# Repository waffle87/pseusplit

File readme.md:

# Pseusplit

A pseudo-split keyboard with a trackpad or LCD display and per-key RGB

## Hardware Specifics
This keyboard uses an integrated STM32G0B1 microcontroller fit with a single push button switch<sup>[1](#references)</sup>, and USB-C. It also features a dedicated IS31FL3733 RGB Matrix driver to alleviate processing power from the primary MCU for LCD drawing, or other tasks.

## Ordering
The following instructions will be for [JLCPCB](jlcpcb.com), but should generally apply to most PCB manufacturers. The Gerber files in this repository include:
- [**pcb_gerbers.zip**](production/pcb_gerbers.zip): Main PCB
- [**plate_gerbers.zip**](production/plate_gerbers.zip): Switch Plate PCB<sup>*</sup>
- [**back_gerbers.zip**](production/back_gerbers.zip): Backplate PCB

* The switch plate PCB is designed for a single half of the keyboard (and is reversible), meaning ordering a quantity of 10 will be enough to cover 5 keyboards.

1. Upload the appropriate Gerber files described above
2. Set PCB quantity and colour as desired
3. For PCB assembly, choose **Economic** PCBA type and **Bottom Side** for assembly side
4. Upload the [BOM](production/bom.csv) and [CPL](production/positions.csv) files
5. Ensure the correct components have been selected, and all are in stock. An effort has been made to choose as few extended components as possible, but this is not possible for some.
6. Give a quick look at the component placement and make sure nothing looks wildly wrong. It is normal for some components to be shown oriented incorrectly or not quite where they belong. The PCB reviewers will usually correct this without issue.

### Additional Components
For optional components to be installed by hand:
| Item | Quantity | Remarks |
|------|----------|---------|
| 6028 RGB LEDs ([Alibaba](https://www.alibaba.com/product-detail/smd-6028-RGB-led-diode-for_60637386884.html)) | 36 | Unforunately, LEDs matching this pinout are rather difficult to find, and are not carried by LCSC. |
| 4mm M2 Screws | 8 | Used for mounting PCB to plate case. Length does not have to be exact. |
| 6mm M2 Standoffs | 4 | Used for mounting PCB to plate case. Ensure maximum diameter is no greater than 4mm. |
| 240x240 LCD ([ST7789](https://www.adafruit.com/product/3787)) | 1<sup>*</sup> | Other displays with same pinout and dimensions (no larger than 40x43mm) will work. |
| Azoteq Trackpad ([TPS43](https://www.mouser.com/ProductDetail/Azoteq/TPS43-201A-B?qs=HXFqYaX1Q2x%252BNkQCZlM0ug%3D%3D)) | 1<sup>*</<sup> | Installed via soldering wires to appropriate display header pins. |
| MX Switches | 36 | Pick your favourite switches! |

* Trackpad and LCD is either/or. Both cannot be installed at the same time.

## Assembly Instructions
These steps assume you already have an assembled PCB and are installing switches, trackpad, etc. If you are hand-assembling the PCBs with all components, the [interactive BOM](https://html-preview.github.io/?url=https://github.com/waffle87/pseusplit/blob/master/ibom.html) will be handy.

1. **Compile and flash firmware.** This assumes a local QMK build environment has already been setup. Firmware sources can be found [here](https://git.pngu.org/qmk_me/keyboards/pseusplit). Enter bootloader by holding the reset button while plugging PCB in. Flash firmware using `qmk flash` or QMK Toolbox.
2. **Ensure the keyboard is functional** by shorting switch footprint pins with metal tweezers. This should output keypresses on the computer.
3. **Install LCD display if desired.** Solder the 12 pin header to the labeled footprint on the PCB and solder display to the header. In the firmware, enable the Quantum Painter feature and disable the Pointing Device feature if necessary.
4. **Install Azoteq trackpad if desired.** Solder wires from the pins on the trackpad to the appropriate pins on the 12 pin header. Refer to schematic for specifics. In the firmware, enable the Pointing Device feature and disable the Quantum Painter feature if necessary.
5. **Install switches** by inserting a few switches into the switch plate (corners/middle), and then solder to PCB. Fill in rest of switches, testing as you go.
6. **Assemble plate case**. Insert the M2 screws into the back plate and affix standoffs to screws. Place PCB + Plate onto standoffs and install remaining 4 screws.

## References
1. [A single-push reset circuit for STM32](https://acheronproject.com/reset_article_1/reset_article_1)
2. Relevant datasheets

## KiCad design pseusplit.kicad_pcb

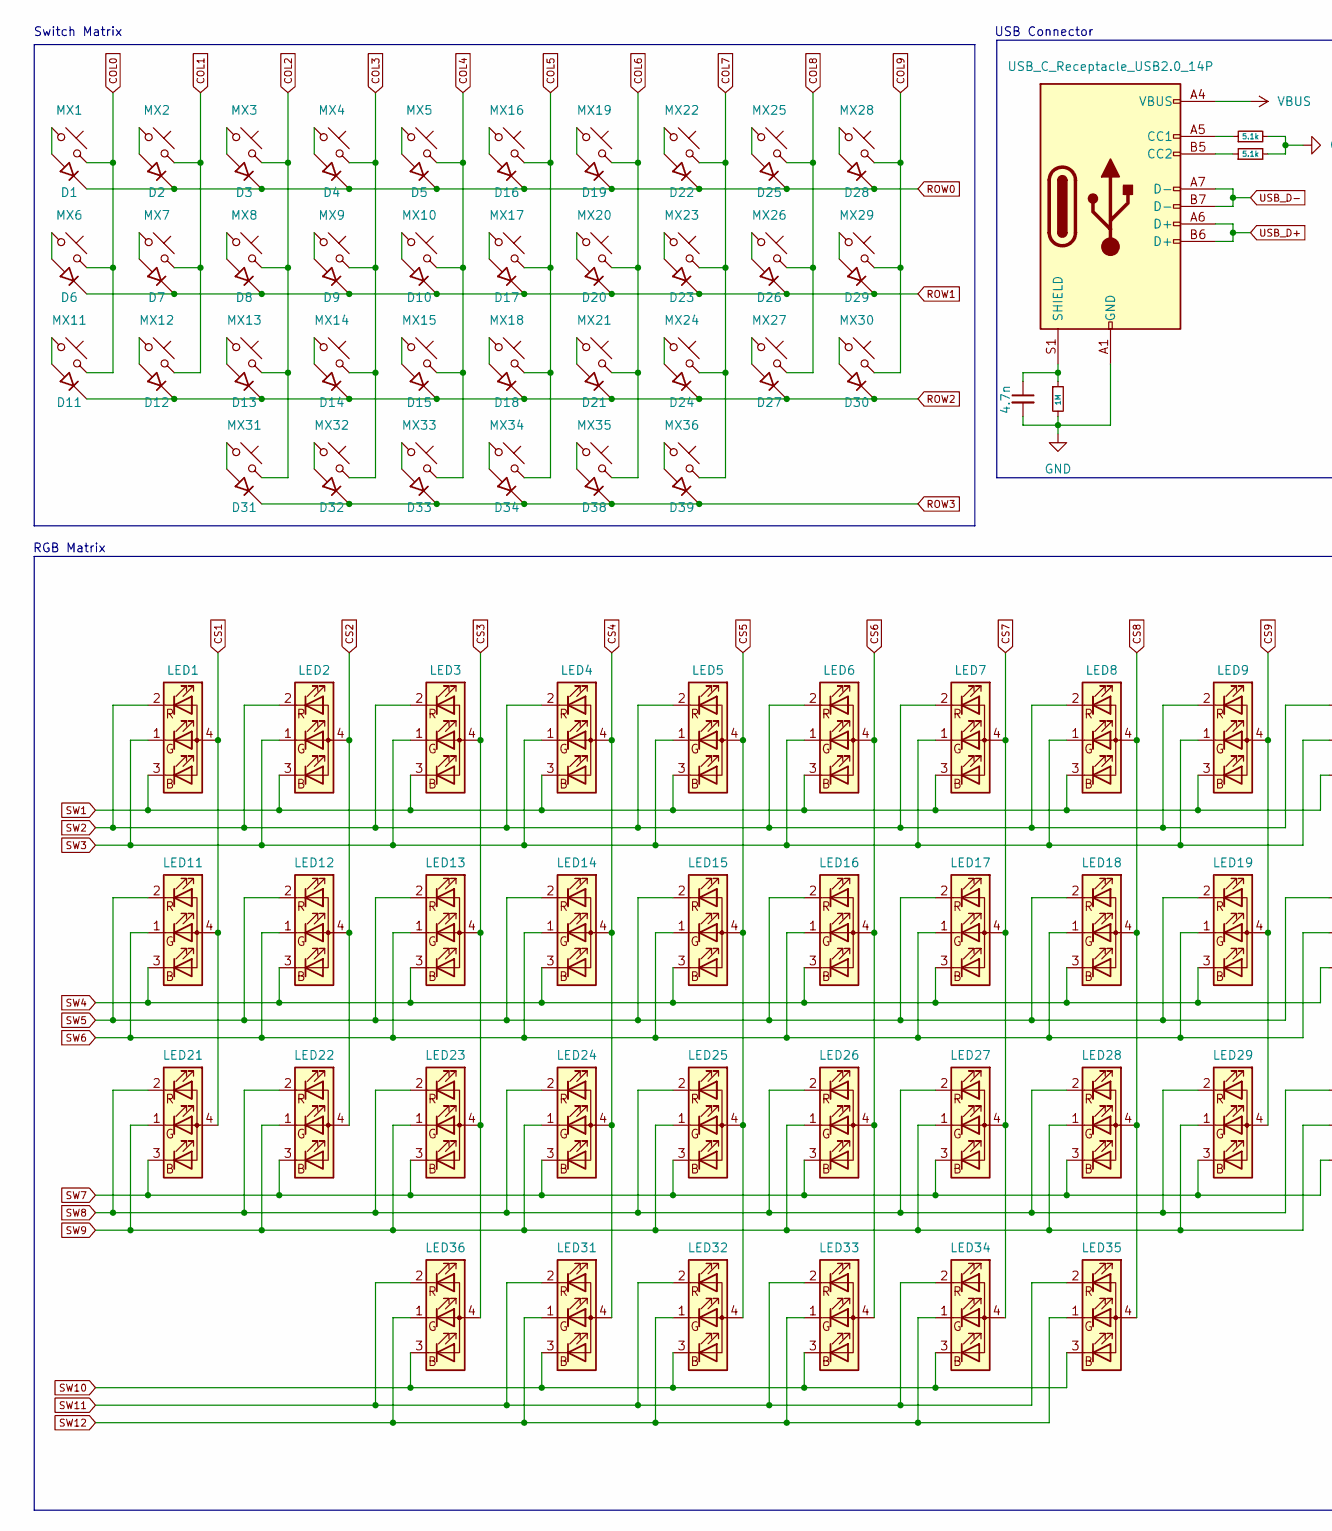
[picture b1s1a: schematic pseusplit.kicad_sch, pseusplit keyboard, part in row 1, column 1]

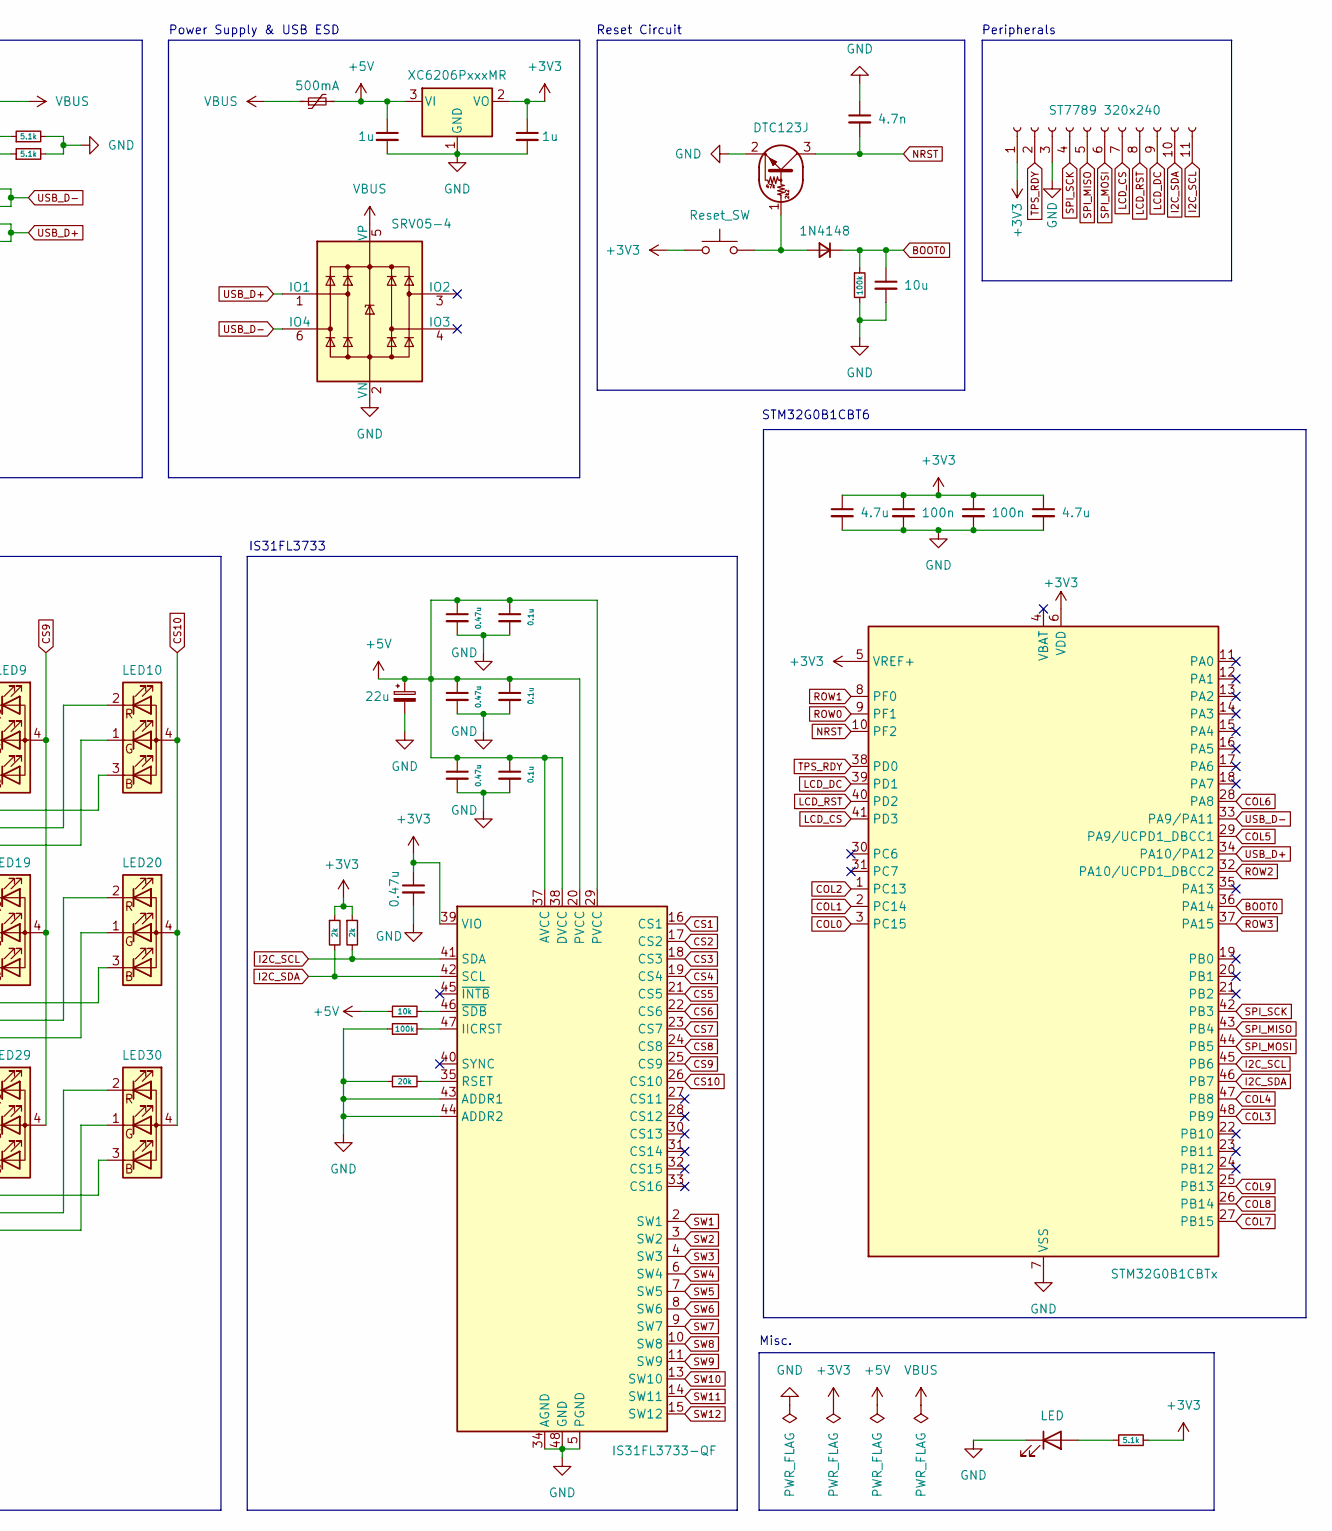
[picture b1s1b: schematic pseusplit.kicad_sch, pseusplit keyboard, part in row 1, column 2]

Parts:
C1, C2, C4, C6: 0.47u; C_0805_2012Metric; MPN C13967
C3, C5, C7: 0.1u; C_0805_2012Metric; MPN C49678
C8: 22u; C_0805_2012Metric; MPN C45783
C9, C12: 4.7n; C_0805_2012Metric; MPN C1744
C10, C11: 1u; C_0805_2012Metric; MPN C28323
C13: 10u; C_0805_2012Metric; MPN C15850
C14, C16: 100n; C_0805_2012Metric; MPN C28233
C17, C18: 4.7u; C_0805_2012Metric; MPN C1779
D1, D2, D3, D4, D5, D6, D7, D8, D9, D10, D11, D12, D13, D14, D15, D16, D17, D18, D19, D20, D21, D22, D23, D24, D25, D26, D27, D28, D29, D30, D31, D32, D33, D34, D38, D39: D_45deg; D_SOD-123; MPN C81598
D37: 1N4148; D_SOD-123; MPN C81598
D40: LED; LED_0805_2012Metric; MPN C2297
F1: 500mA; Fuse_1206_3216Metric; MPN C2830238
J1: USB_C_Receptacle_USB2.0_14P; USB_C_Receptacle_HRO_TYPE-C-31-M-12; MPN C165948
J3: ST7789 320x240; PinHeader_1x11_P2.54mm_Vertical
LED1, LED2, LED3, LED4, LED5, LED6, LED7, LED8, LED9, LED10, LED11, LED12, LED13, LED14, LED15, LED16, LED17, LED18, LED19, LED20, LED21, LED22, LED23, LED24, LED25, LED26, LED27, LED28, LED29, LED30, LED31, LED32, LED33, LED34, LED35, LED36: MX_LED_6028R; LED_MX_6028R; MPN C183826
MX1: Q; SW_MX_1u
MX2: W; SW_MX_1u
MX3: E; SW_MX_1u
MX4: R; SW_MX_1u
MX5: T; SW_MX_1u
MX6: A; SW_MX_1u
MX7: S; SW_MX_1u
MX8: D; SW_MX_1u
MX9: F; SW_MX_1u
MX10: G; SW_MX_1u
MX11: Z; SW_MX_1u
MX12: X; SW_MX_1u
MX13: C; SW_MX_1u
MX14: V; SW_MX_1u
MX15: B; SW_MX_1u
MX16: Y; SW_MX_1u
MX17: H; SW_MX_1u
MX18: N; SW_MX_1u
MX19: U; SW_MX_1u
MX20: J; SW_MX_1u
MX21: M; SW_MX_1u
MX22: I; SW_MX_1u
MX23: K; SW_MX_1u
MX24: ,; SW_MX_1u
MX25: O; SW_MX_1u
MX26: L; SW_MX_1u
MX27: .; SW_MX_1u
MX28: P; SW_MX_1u
MX29: ;; SW_MX_1u
MX30: /; SW_MX_1u
MX31: T1; SW_MX_1u
MX32: T2; SW_MX_1u
MX33: T3; SW_MX_1u
MX34: T4; SW_MX_1u
MX35: T5; SW_MX_1u
MX36: T6; SW_MX_1u
Q1: DTC123J; SOT-23; MPN C20616358
R1: 20k; R_0805_2012Metric; MPN C4328
R2, R11: 100k; R_0805_2012Metric; MPN C149504
R3: 10k; R_0805_2012Metric; MPN C17414
R4, R5: 2k; R_0805_2012Metric; MPN C17604
R6: 1M; R_0805_2012Metric; MPN C17514
R7, R8, R12: 5.1k; R_0805_2012Metric; MPN C27834
SW1: Reset_SW; SW_SPST_SKQG_WithStem; MPN C318884
U1: IS31FL3733-QF; QFN-48-1EP_6x6mm_P0.4mm_EP4.2x4.2mm; MPN C506251
U2: XC6206PxxxMR; SOT-23-3; MPN C5446
U4: STM32G0B1CBTx; LQFP-48_7x7mm_P0.5mm; MPN C2847904
U5: SRV05-4; SOT-23-6-routable; MPN C558418

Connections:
+3V3: C1.1, C11.1, C14.1, C16.1, C17.1, C18.1, J3.1, R4.1, R5.1, R12.2, SW1.1, U1.39 (VIO), U2.2 (VO), U4.5 (VREF+), U4.6 (VDD)
+5V: C2.1, C3.1, C4.1, C5.1, C6.1, C7.1, C8.1, C10.1, F1.2, R3.1, U1.20 (PVCC), U1.29 (PVCC), U1.37 (AVCC), U1.38 (DVCC), U2.3 (VI)
BOOT0: C13.1, D37.1 (K), R11.1, U4.36 (PA14)
COL0: MX1.2, MX6.2, MX11.2, U4.3 (PC15)
COL1: MX2.2, MX7.2, MX12.2, U4.2 (PC14)
COL2: MX3.2, MX8.2, MX13.2, MX31.2, U4.1 (PC13)
COL3: MX4.2, MX9.2, MX14.2, MX32.2, U4.48 (PB9)
COL4: MX5.2, MX10.2, MX15.2, MX33.2, U4.47 (PB8)
COL5: MX16.2, MX17.2, MX18.2, MX34.2, U4.29 (PA9/UCPD1_DBCC1)
COL6: MX19.2, MX20.2, MX21.2, MX35.2, U4.28 (PA8)
COL7: MX22.2, MX23.2, MX24.2, MX36.2, U4.27 (PB15)
COL8: MX25.2, MX26.2, MX27.2, U4.26 (PB14)
COL9: MX28.2, MX29.2, MX30.2, U4.25 (PB13)
CS1: LED1.4 (A), LED11.4 (A), LED21.4 (A), U1.16 (CS1)
CS2: LED2.4 (A), LED12.4 (A), LED22.4 (A), U1.17 (CS2)
CS3: LED3.4 (A), LED13.4 (A), LED23.4 (A), LED36.4 (A), U1.18 (CS3)
CS4: LED4.4 (A), LED14.4 (A), LED24.4 (A), LED31.4 (A), U1.19 (CS4)
CS5: LED5.4 (A), LED15.4 (A), LED25.4 (A), LED32.4 (A), U1.21 (CS5)
CS6: LED6.4 (A), LED16.4 (A), LED26.4 (A), LED33.4 (A), U1.22 (CS6)
CS7: LED7.4 (A), LED17.4 (A), LED27.4 (A), LED34.4 (A), U1.23 (CS7)
CS8: LED8.4 (A), LED18.4 (A), LED28.4 (A), LED35.4 (A), U1.24 (CS8)
CS9: LED9.4 (A), LED19.4 (A), LED29.4 (A), U1.25 (CS9)
CS10: LED10.4 (A), LED20.4 (A), LED30.4 (A), U1.26 (CS10)
GND: C1.2, C2.2, C3.2, C4.2, C5.2, C6.2, C7.2, C8.2, C9.2, C10.2, C11.2, C12.1, C13.2, C14.2, C16.2, C17.2, C18.2, D40.1 (K), J1.A1 (GND), J1.A12 (GND), J1.B1 (GND), J1.B12 (GND), J3.3, Q1.2 (E), R1.1, R2.1, R6.2, R7.2, R8.2, R11.2, U1.5 (PGND), U1.12 (PGND), U1.34 (AGND), U1.43 (ADDR1), U1.44 (ADDR2), U1.48 (GND), U1.49 (GND), U2.1 (GND), U4.7 (VSS), U5.2 (VN)
I2C_SCL: J3.11, R5.2, U1.41 (SDA), U4.45 (PB6)
I2C_SDA: J3.10, R4.2, U1.42 (SCL), U4.46 (PB7)
LCD_CS: J3.7, U4.41 (PD3)
LCD_DC: J3.9, U4.39 (PD1)
LCD_RST: J3.8, U4.40 (PD2)
NRST: C12.2, Q1.3 (C), U4.10 (PF2)
unnamed: D1.2 (A), MX1.1
unnamed: D2.2 (A), MX2.1
unnamed: D3.2 (A), MX3.1
unnamed: D4.2 (A), MX4.1
unnamed: D5.2 (A), MX5.1
unnamed: D6.2 (A), MX6.1
unnamed: D7.2 (A), MX7.1
unnamed: D8.2 (A), MX8.1
unnamed: D9.2 (A), MX9.1
unnamed: D10.2 (A), MX10.1
unnamed: D11.2 (A), MX11.1
unnamed: D12.2 (A), MX12.1
unnamed: D13.2 (A), MX13.1
unnamed: D14.2 (A), MX14.1
unnamed: D15.2 (A), MX15.1
unnamed: D16.2 (A), MX16.1
unnamed: D17.2 (A), MX17.1
unnamed: D18.2 (A), MX18.1
unnamed: D19.2 (A), MX19.1
unnamed: D20.2 (A), MX20.1
unnamed: D21.2 (A), MX21.1
unnamed: D22.2 (A), MX22.1
unnamed: D23.2 (A), MX23.1
unnamed: D24.2 (A), MX24.1
unnamed: D25.2 (A), MX25.1
unnamed: D26.2 (A), MX26.1
unnamed: D27.2 (A), MX27.1
unnamed: D28.2 (A), MX28.1
unnamed: D29.2 (A), MX29.1
unnamed: D30.2 (A), MX30.1
unnamed: D31.2 (A), MX31.1
unnamed: D32.2 (A), MX32.1
unnamed: D33.2 (A), MX33.1
unnamed: D34.2 (A), MX34.1
unnamed: D37.2 (A), Q1.1 (B), SW1.2
unnamed: D38.2 (A), MX35.1
unnamed: D39.2 (A), MX36.1
unnamed: D40.2 (A), R12.1
unnamed: J1.A5 (CC1), R7.1
unnamed: J1.B5 (CC2), R8.1
unnamed: C9.1, J1.S1 (SHIELD), R6.1
unnamed: R2.2, U1.47 (IICRST)
unnamed: R1.2, U1.35 (RSET)
unnamed: R3.2, U1.46 (~SDB)
ROW0: D1.1 (K), D2.1 (K), D3.1 (K), D4.1 (K), D5.1 (K), D16.1 (K), D19.1 (K), D22.1 (K), D25.1 (K), D28.1 (K), U4.9 (PF1)
ROW1: D6.1 (K), D7.1 (K), D8.1 (K), D9.1 (K), D10.1 (K), D17.1 (K), D20.1 (K), D23.1 (K), D26.1 (K), D29.1 (K), U4.8 (PF0)
ROW2: D11.1 (K), D12.1 (K), D13.1 (K), D14.1 (K), D15.1 (K), D18.1 (K), D21.1 (K), D24.1 (K), D27.1 (K), D30.1 (K), U4.32 (PA10/UCPD1_DBCC2)
ROW3: D31.1 (K), D32.1 (K), D33.1 (K), D34.1 (K), D38.1 (K), D39.1 (K), U4.37 (PA15)
SPI_MISO: J3.5, U4.43 (PB4)
SPI_MOSI: J3.6, U4.44 (PB5)
SPI_SCK: J3.4, U4.42 (PB3)
SW1: LED1.3 (BK), LED2.3 (BK), LED3.3 (BK), LED4.3 (BK), LED5.3 (BK), LED6.3 (BK), LED7.3 (BK), LED8.3 (BK), LED9.3 (BK), LED10.3 (BK), U1.2 (SW1)
SW2: LED1.2 (RK), LED2.2 (RK), LED3.2 (RK), LED4.2 (RK), LED5.2 (RK), LED6.2 (RK), LED7.2 (RK), LED8.2 (RK), LED9.2 (RK), LED10.2 (RK), U1.3 (SW2)
SW3: LED1.1 (GK), LED2.1 (GK), LED3.1 (GK), LED4.1 (GK), LED5.1 (GK), LED6.1 (GK), LED7.1 (GK), LED8.1 (GK), LED9.1 (GK), LED10.1 (GK), U1.4 (SW3)
SW4: LED11.3 (BK), LED12.3 (BK), LED13.3 (BK), LED14.3 (BK), LED15.3 (BK), LED16.3 (BK), LED17.3 (BK), LED18.3 (BK), LED19.3 (BK), LED20.3 (BK), U1.6 (SW4)
SW5: LED11.2 (RK), LED12.2 (RK), LED13.2 (RK), LED14.2 (RK), LED15.2 (RK), LED16.2 (RK), LED17.2 (RK), LED18.2 (RK), LED19.2 (RK), LED20.2 (RK), U1.7 (SW5)
SW6: LED11.1 (GK), LED12.1 (GK), LED13.1 (GK), LED14.1 (GK), LED15.1 (GK), LED16.1 (GK), LED17.1 (GK), LED18.1 (GK), LED19.1 (GK), LED20.1 (GK), U1.8 (SW6)
SW7: LED21.3 (BK), LED22.3 (BK), LED23.3 (BK), LED24.3 (BK), LED25.3 (BK), LED26.3 (BK), LED27.3 (BK), LED28.3 (BK), LED29.3 (BK), LED30.3 (BK), U1.9 (SW7)
SW8: LED21.2 (RK), LED22.2 (RK), LED23.2 (RK), LED24.2 (RK), LED25.2 (RK), LED26.2 (RK), LED27.2 (RK), LED28.2 (RK), LED29.2 (RK), LED30.2 (RK), U1.10 (SW8)
SW9: LED21.1 (GK), LED22.1 (GK), LED23.1 (GK), LED24.1 (GK), LED25.1 (GK), LED26.1 (GK), LED27.1 (GK), LED28.1 (GK), LED29.1 (GK), LED30.1 (GK), U1.11 (SW9)
SW10: LED31.3 (BK), LED32.3 (BK), LED33.3 (BK), LED34.3 (BK), LED35.3 (BK), LED36.3 (BK), U1.13 (SW10)
SW11: LED31.2 (RK), LED32.2 (RK), LED33.2 (RK), LED34.2 (RK), LED35.2 (RK), LED36.2 (RK), U1.14 (SW11)
SW12: LED31.1 (GK), LED32.1 (GK), LED33.1 (GK), LED34.1 (GK), LED35.1 (GK), LED36.1 (GK), U1.15 (SW12)
TPS_RDY: J3.2, U4.38 (PD0)
USB_D+: J1.A6 (D+), J1.B6 (D+), U4.34 (PA10/PA12), U5.1 (IO1)
USB_D-: J1.A7 (D-), J1.B7 (D-), U4.33 (PA9/PA11), U5.6 (IO4)
VBUS: F1.1, J1.A4 (VBUS), J1.A9 (VBUS), J1.B4 (VBUS), J1.B9 (VBUS), U5.5 (VP)

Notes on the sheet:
IS31FL3733
RGB Matrix
STM32G0B1CBT6
Power Supply & USB ESD
USB Connector
Misc.
Reset Circuit
Switch Matrix
Peripherals

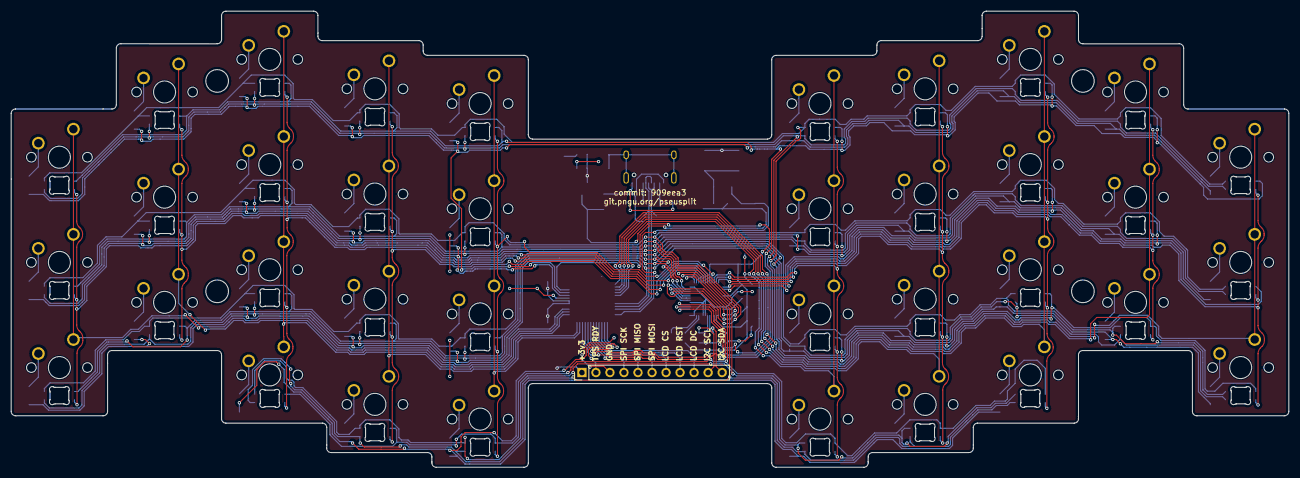
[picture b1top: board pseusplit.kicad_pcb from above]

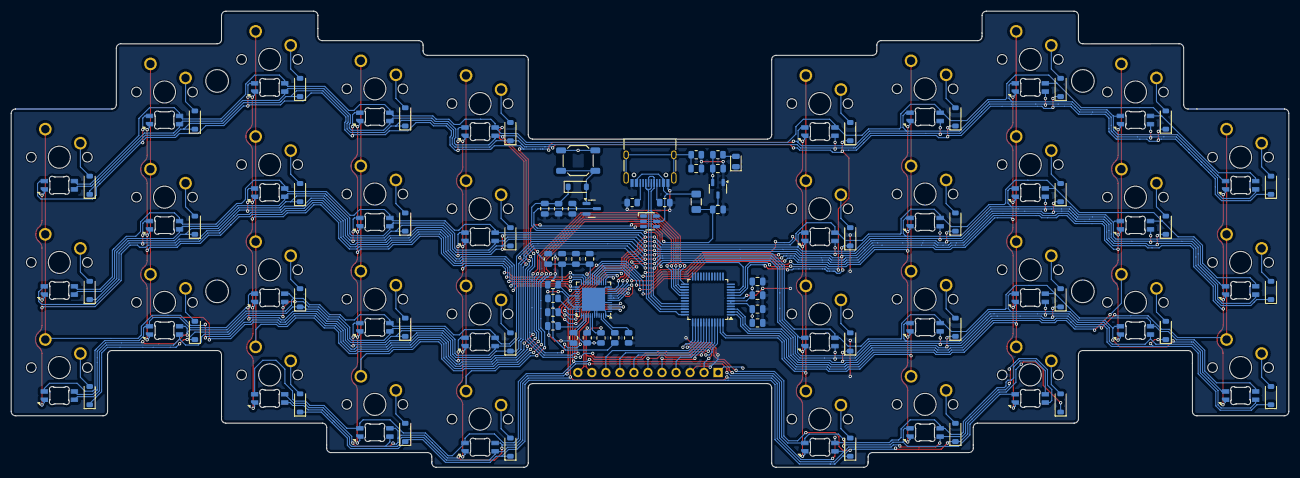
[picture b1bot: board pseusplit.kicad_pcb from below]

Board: 2 copper layers, 231.4 x 82.6 mm, 146 parts (109 on the bottom side), 97 nets.

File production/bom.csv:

Designator,Footprint,Quantity,Value,LCSC Part #
"C1, C2, C4, C6",0805,4,0.47u,C13967
"C10, C11",0805,2,1u,C28323
"C12, C9",0805,2,4.7n,C1744
C13,0805,1,10u,C15850
"C14, C16",0805,2,100n,C28233
"C17, C18",0805,2,4.7u,C1779
"C3, C5, C7",0805,3,0.1u,C49678
C8,0805,1,22u,C45783
"D1, D10, D11, D12, D13, D14, D15, D16, D17, D18, D19, D2, D20, D21, D22, D23, D24, D25, D26, D27, D28, D29, D3, D30, D31, D32, D33, D34, D38, D39, D4, D5, D6, D7, D8, D9",D_SOD-123,36,D_45deg,C81598
D37,D_SOD-123,1,1N4148,C81598
D40,0805,1,LED,C2297
F1,1206,1,500mA,C2830238
J1,USB_C_Receptacle_HRO_TYPE-C-31-M-12,1,USB_C_Receptacle_USB2.0_14P,C165948
"LED1, LED10, LED11, LED12, LED13, LED14, LED15, LED16, LED17, LED18, LED19, LED2, LED20, LED21, LED22, LED23, LED24, LED25, LED26, LED27, LED28, LED29, LED3, LED30, LED31, LED32, LED33, LED34, LED35, LED36, LED4, LED5, LED6, LED7, LED8, LED9",LED_MX_6028R,36,MX_LED_6028R,C183826
Q1,SOT-23,1,DTC123J,C20616358
R1,0805,1,20k,C4328
"R11, R2",0805,2,100k,C149504
"R12, R7, R8",0805,3,5.1k,C27834
R3,0805,1,10k,C17414
"R4, R5",0805,2,2k,C17604
R6,0805,1,1M,C17514
SW1,SW_SPST_SKQG_WithStem,1,Reset_SW,C318884
U1,QFN-48-1EP_6x6mm_P0.4mm_EP4.2x4.2mm,1,IS31FL3733-QF,C506251
U2,SOT-23-3,1,XC6206PxxxMR,C5446
U4,LQFP-48_7x7mm_P0.5mm,1,STM32G0B1CBTx,C2847904
U5,SOT-23-6-routable,1,SRV05-4,C558418

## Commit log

2025-06-16 Add PCBs (eletronic, backplate, switchplate), production files, and initial documentation
2025-06-16 Add silkscreen graphics and SVG images
2025-06-16 Update some part numbers, remove unnecessary MPN symbol field, dos2unix CSV files
2025-06-27 Update tantalum capacitor footprint & part, remove LEDs from BOM & provide link
2025-06-27 Update silkscreen graphics, IBOM, gerbers, and readme typo
2025-06-28 Some readme fixes and correct part number from SOT-523 -> SOT23
